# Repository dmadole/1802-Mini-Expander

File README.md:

# 1802-Mini-Expander-RTC
This is the memory and port expander plus real-time clock card for the [1802/Mini](https://github.com/dmadole/1802-Mini) system. It supports the following features:

### Memory Expansion

* 32K added ROM or RAM
* Can be addressed in either upper or lower 32K block
* Can be split on any power of 2 size from the top or bottom of the block
* Splitting the block allows mixed ROM and RAM in the same 32K block
* Expansion memory can be enabled or disabled under software control
* Can be set to be enabled or disabled be default at system reset

The software control can be used to implement bank switching, such a 32K ROM that includes diagnostics run at boot time but is then replaced with RAM except for the last 2K or 4K which has BIOS. Or you could have a system that can start either a Riley “Disk-less ROM” with 32K RAM/32K ROM, or a Elf/OS system with 60K RAM/2K ROM under control of a software menu.

### Real Time Clock

* Keeps month, day, year, hour, minute, second time and date
* Corrects for leap years
* Can provide a periodic interrupt at 64 Hz or once per second, minute, or hour
* Can also provide a pollable signal on an EF line at the same rates
* Uses a replaceable BR1225 coin cell battery
* 1.3uA standby current gives approximately 5 years battery life
* Uses one I/O port 1-7 which is two-level group addressable

I have written a loadable driver that presents the “standard” interface to Elf/OS 4 to enable date and time, and there is also a new BIOS that supports all features of this card available here:

> https://github.com/dmadole/1802-Mini/tree/master/firmware

### Port Expander

* Implements low 4 bits of the Microboard group scheme
* Written group select value can be read back also
* Implements a “group 0” which is automatically selected at reset
* Total of 5 groups gives 35 maximum I/O ports (5 groups of 7)
* Allows for high 4 bits to be implemented on another card
* Uses one I/O port 1-7

Gerber files for the PCBs and PDF schematics can be found in [Releases](https://github.com/dmadole/1802-Mini-Expander-RTC/releases).

BOMS and any applicable errata or other notes can be found in [notes](https://github.com/dmadole/1802-Mini-Expander-RTC/tree/main/notes).

For availability of kits and bare PCBs please see http://madole.net/1802/mini/kits

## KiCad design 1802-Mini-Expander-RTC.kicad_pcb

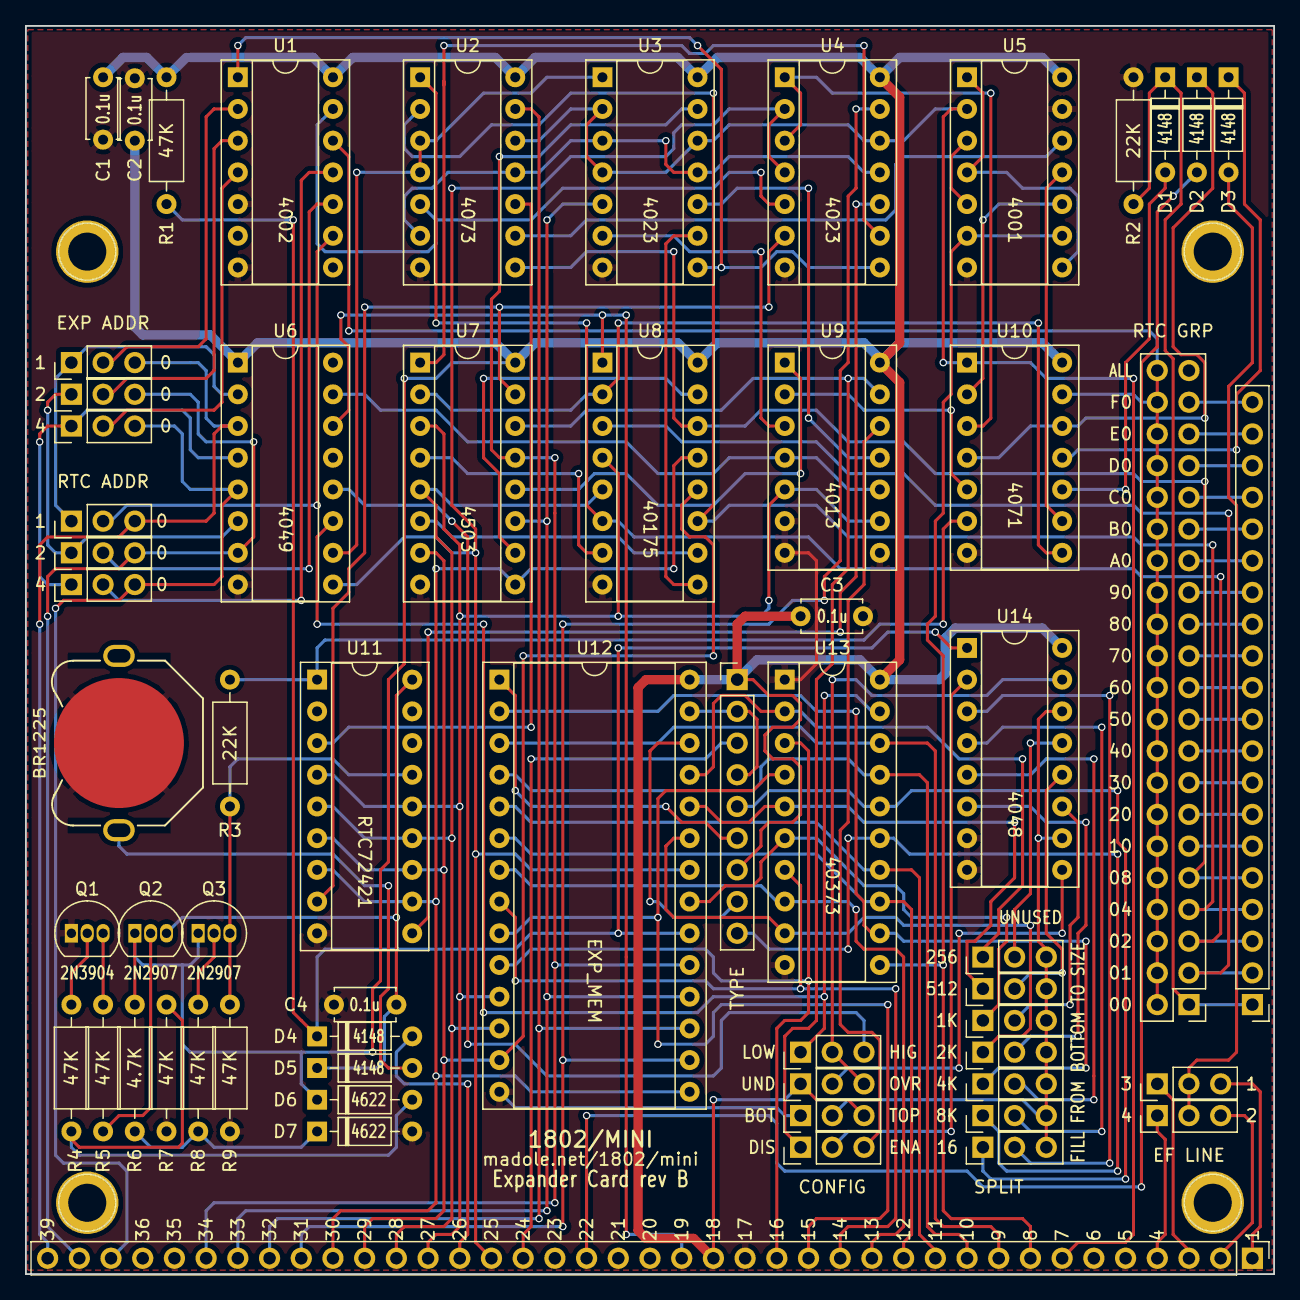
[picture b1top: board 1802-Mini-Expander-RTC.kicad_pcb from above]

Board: 2 copper layers, 100.0 x 100.0 mm, 65 parts (0 on the bottom side), 126 nets.

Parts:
BT1: BR1225; Keystone 3001
C1, C2, C3, C4: 0.1u; C_Disc_D4.7mm_W2.5mm_P5.00mm
D1, D2, D3, D4, D5: 1N4148; D_DO-35_SOD27_P7.62mm_Horizontal
D6, D7: 1N4622; D_DO-35_SOD27_P7.62mm_Horizontal
J1, J2, J3, J4: Mount; 1pin
J5: Conn_01x20; PinHeader_1x20_P2.54mm_Vertical
J6: Conn_02x21_Odd_Even; PinHeader_2x21_P2.54mm_Vertical
J7: Expansion; Pin_Header_Straight_1x39_Pitch2.54mm
JP1: SLOT_3_CONFIG; PinHeader_1x09_P2.54mm_Vertical
JP2, JP5: N0; PinHeader_1x03_P2.54mm_Vertical
JP3, JP6: N1; PinHeader_1x03_P2.54mm_Vertical
JP4, JP7: N2; PinHeader_1x03_P2.54mm_Vertical
JP8: HI/LOW; PinHeader_1x03_P2.54mm_Vertical
JP9: BOT/TOP; PinHeader_1x03_P2.54mm_Vertical
JP10: A8; PinHeader_1x03_P2.54mm_Vertical
JP11: A10; PinHeader_1x03_P2.54mm_Vertical
JP12: A11; PinHeader_1x03_P2.54mm_Vertical
JP13: A12; PinHeader_1x03_P2.54mm_Vertical
JP14: A13; PinHeader_1x03_P2.54mm_Vertical
JP15: A14; PinHeader_1x03_P2.54mm_Vertical
JP16: OVR/UND; PinHeader_1x03_P2.54mm_Vertical
JP17: A9; PinHeader_1x03_P2.54mm_Vertical
JP18: ENA/DIS; PinHeader_1x03_P2.54mm_Vertical
JP19: EF1/EF3; PinHeader_1x03_P2.54mm_Vertical
JP20: EF2/EF4; PinHeader_1x03_P2.54mm_Vertical
Q1: 2N3904; TO-92_Inline
Q2, Q3: 2N2907; TO-92_Inline
R1, R4, R5, R7, R8, R9: 47K; R_Axial_DIN0207_L6.3mm_D2.5mm_P10.16mm_Horizontal
R2, R3: 22K; R_Axial_DIN0207_L6.3mm_D2.5mm_P10.16mm_Horizontal
R6: 4.7K; R_Axial_DIN0207_L6.3mm_D2.5mm_P10.16mm_Horizontal
U1: 4002; DIP-14_W7.62mm_Socket
U2: 4073; DIP-14_W7.62mm_Socket
U3, U4: 4023; DIP-14_W7.62mm_Socket
U5: 4001; DIP-14_W7.62mm_Socket
U6: 4049; DIP-16_W7.62mm_Socket
U7: 4503; DIP-16_W7.62mm_Socket
U8: 40175; DIP-16_W7.62mm_Socket
U9: 4013; DIP-14_W7.62mm_Socket
U10: 4071; DIP-14_W7.62mm_Socket
U11: RTC72421; DIP-18_W7.62mm_Socket
U12: EXP_MEM; DIP-28_W15.24mm_Socket
U13: 40373; DIP-20_W7.62mm_Socket
U14: 4048; DIP-16_W7.62mm_Socket

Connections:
+BATT: C4.1, D5.1, Q2.3, U11.18
/BUS0: J7.27, U7.3, U8.4, U9.5, U9.9, U11.4, U11.14, U12.11
/BUS1: J7.28, U7.5, U8.5, U11.5, U11.13, U12.12
/BUS2: J7.29, U7.7, U8.12, U11.6, U11.12, U12.13
/BUS3: J7.30, U7.9, U8.13, U11.7, U11.11, U12.15
/BUS4: J7.31, U4.13, U12.16
/BUS5: J7.32, U2.13, U12.17
/BUS6: J7.33, U3.5, U7.11, U12.18
/BUS7: J7.34, U3.13, U7.13, U12.19
/MA0: J7.16, U12.10, U13.3
/MA1: J7.15, U12.9, U13.4
/MA2: J7.14, U12.8, U13.7
/MA3: J7.13, U12.7, U13.8
/MA4: J7.12, U12.6, U13.13
/MA5: J7.11, U12.5, U13.14
/MA6: J7.10, U12.4, U13.17
/MA7: J7.9, U12.3, U13.18
CLEAR: U6.15, U9.4, U9.10
GND: BT1.2, C1.2, C2.2, C3.2, C4.2, D7.2, J6.41, J7.17, JP9.1, Q1.1, R2.2, R7.2, R9.2, U1.5, U1.7, U2.7, U3.7, U4.7, U5.7, U5.13, U6.8, U7.8, U8.8, U9.6, U9.7, U9.8, U10.7, U11.2, U11.9, U12.14, U13.1, U13.10, U14.7, U14.8
MEN: D4.2, J7.26
N0: J7.39, JP2.3, JP5.3, U6.3
N1: J7.38, JP3.3, JP6.3, U6.7
N2: J7.37, JP4.3, JP7.3, U6.5
unnamed: BT1.1, D5.2
unnamed: D1.1, J5.1, J6.1, R2.1
unnamed: D1.2, U10.10
unnamed: D2.1, U10.4, U10.12
unnamed: D3.1, U10.11
unnamed: D3.2, JP19.2, JP20.2
unnamed: D4.1, R1.2, U12.20, U14.1
unnamed: D6.2, R4.1, R7.1
unnamed: D7.1, R6.2, R8.1
unnamed: J5.2, J6.3, U8.3
unnamed: J5.3, J6.5, U2.1, U8.6
unnamed: J5.4, J6.7, U2.2, U8.11
unnamed: J5.5, J6.9, U2.8, U8.14
unnamed: J5.6, J6.11
unnamed: J5.7, J6.13
unnamed: J5.8, J6.15
unnamed: J5.9, J6.17
unnamed: J5.10, J6.19
unnamed: J5.11, J6.21
unnamed: J5.12, J6.23
unnamed: J5.13, J6.25
unnamed: J5.14, J6.27
unnamed: J5.15, J6.29
unnamed: J5.16, J6.31
unnamed: J5.17, J6.33
unnamed: J5.18, J6.35
unnamed: J5.19, J6.37
unnamed: J5.20, J6.39
unnamed: JP1.2, JP1.4, U12.27
unnamed: JP1.5, JP15.1, U13.16
unnamed: JP1.6, U12.1
unnamed: JP1.8, U12.26
unnamed: JP1.9, JP14.1, U13.15
unnamed: JP2.1, JP5.1, U6.2
unnamed: JP2.2, U1.2
unnamed: JP3.1, JP6.1, U6.6
unnamed: JP3.2, U1.3
unnamed: JP4.1, JP7.1, U6.4
unnamed: JP4.2, U1.4
unnamed: JP5.2, U1.9
unnamed: JP6.2, U1.10
unnamed: JP7.2, U1.11
unnamed: JP8.1, U6.11, U13.19
unnamed: JP8.3, U6.12
unnamed: JP10.1, U12.25, U13.2
unnamed: JP10.2, U14.13
unnamed: JP9.2, JP10.3, JP11.3, JP12.3, JP13.3, JP14.3, JP15.3, JP17.3, U14.10, U14.14
unnamed: JP11.1, U12.21, U13.6
unnamed: JP11.2, U14.11
unnamed: JP12.1, U12.23, U13.9
unnamed: JP12.2, U14.6
unnamed: JP13.1, U12.2, U13.12
unnamed: JP13.2, U14.5
unnamed: JP14.2, U14.4
unnamed: JP15.2, U14.3
unnamed: JP16.2, U14.9
unnamed: JP8.2, JP16.3, U14.15
unnamed: JP17.1, U12.24, U13.5
unnamed: JP17.2, U14.12
unnamed: JP18.1, U7.14, U9.13
unnamed: JP18.2, U14.2
unnamed: JP18.3, U9.12
unnamed: Q1.2, R4.2
unnamed: Q1.3, R5.1
unnamed: Q2.2, R5.2
unnamed: Q3.2, R8.2
unnamed: R3.2, U10.6, U11.1
unnamed: U1.1, U3.8, U4.8
unnamed: U1.13, U2.5, U4.5
unnamed: U2.3, U2.4, U3.1, U6.10
unnamed: U2.9, U5.12
unnamed: U2.6, U2.11, U3.3, U3.11, U4.11
unnamed: U5.1, U5.4, U5.8
unnamed: U5.3, U5.5
unnamed: U7.4, U8.7
unnamed: U7.6, U8.10
unnamed: U7.10, U8.15
unnamed: U7.12, U9.1
unnamed: U5.10, U10.2
unnamed: U4.1, U4.3, U10.3
unnamed: U9.2, U10.5
unnamed: U7.2, U8.2, U10.8
unnamed: U5.11, U10.9
POK: Q3.3, R3.1, R9.1, U11.15
RTCAD: U2.10, U11.3
TPA: J7.8, U5.6, U5.9, U13.11
TPB: J7.7, U2.12, U3.2, U3.4, U3.12, U4.12, U5.2, U10.1
VCC: C1.1, C2.1, C3.1, D6.1, J7.18, JP1.1, JP1.7, JP9.3, JP16.1, Q2.1, Q3.1, R1.1, R6.1, U1.14, U2.14, U3.14, U4.14, U5.14, U6.1, U7.16, U8.16, U9.14, U10.14, U12.28, U13.20, U14.16
~CLEAR: J7.19, U6.14, U8.1
~EF1: J7.1, JP19.3
~EF2: J7.2, JP20.3
~EF3: J7.3, JP19.1
~EF4: J7.4, JP20.1
~GRP: J6.2, J6.4, J6.6, J6.8, J6.10, J6.12, J6.14, J6.16, J6.18, J6.20, J6.22, J6.24, J6.26, J6.28, J6.30, J6.32, J6.34, J6.36, J6.38, J6.40, J6.42, U1.12, U10.13
~GRPRD: U4.9, U7.1
~GRPWR: U3.9, U8.9
~INT: D2.2, J7.22
~INTWR: U3.6, U9.3
~MEMWR: U3.10, U9.11
~MRD: J7.25, U4.2, U4.4, U6.9, U12.22
~MWR: J7.24, JP1.3
~RTCRD: U4.6, U7.15, U11.8
~RTCWR: U4.10, U11.10

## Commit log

2022-05-19 Add image
